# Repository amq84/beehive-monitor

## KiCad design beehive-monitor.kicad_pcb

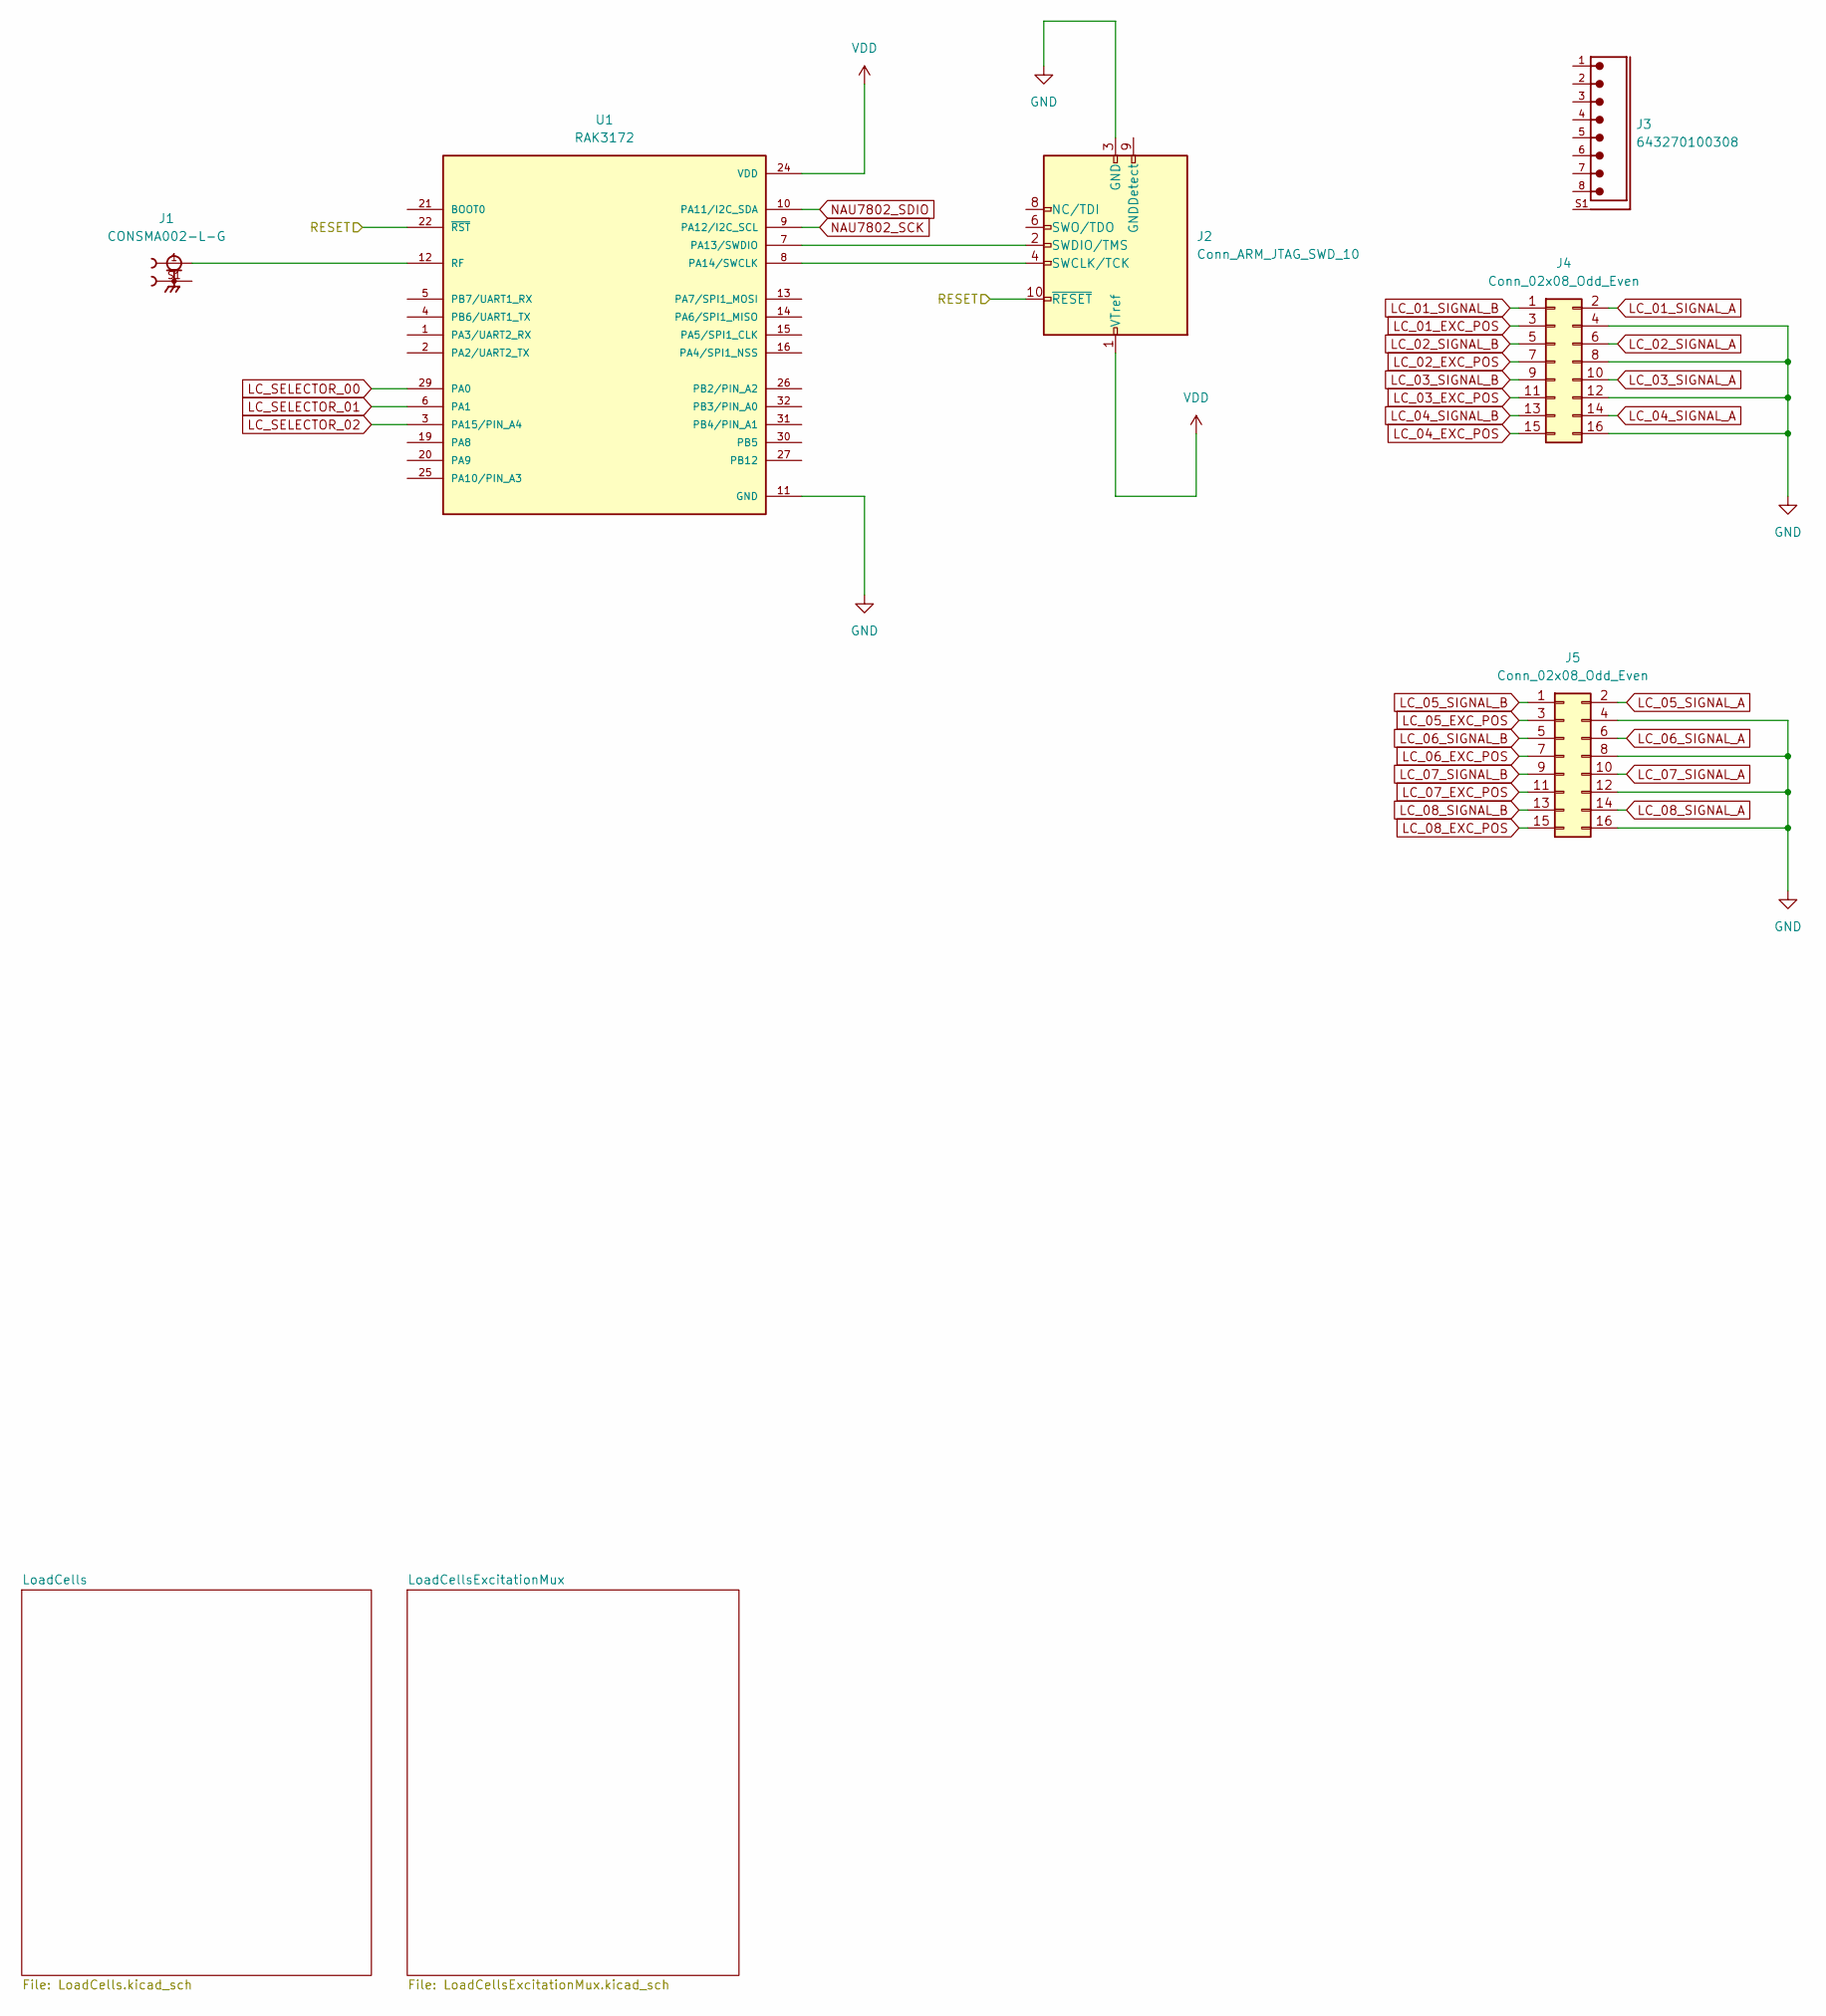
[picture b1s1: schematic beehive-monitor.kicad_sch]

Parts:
J1: CONSMA002-L-G; LINX_CONSMA002-L-G
J2: Conn_ARM_JTAG_SWD_10; PinHeader_2x05_P1.27mm_Vertical
J3: 643270100308
J4, J5: Conn_02x08_Odd_Even; PinHeader_2x08_P2.54mm_Horizontal
U1: RAK3172; XCVR_RAK3172; PARTREV 20/02/2026

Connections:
/RESET: J2.10 (~RESET), U1.22 (~RST)
GND: J2.3 (GND), J2.5 (GND), J4.4, J4.8, J4.12, J4.16, J5.4, J5.8, J5.12, J5.16, U1.11 (GND), U1.17 (GND), U1.18 (GND), U1.23 (GND), U1.28 (GND); also elsewhere on the board
LC_01_EXC_POS: J4.3; also elsewhere on the board
LC_01_SIGNAL_A: J4.2; also elsewhere on the board
LC_01_SIGNAL_B: J4.1; also elsewhere on the board
LC_02_EXC_POS: J4.7; also elsewhere on the board
LC_02_SIGNAL_A: J4.6; also elsewhere on the board
LC_02_SIGNAL_B: J4.5; also elsewhere on the board
LC_03_EXC_POS: J4.11; also elsewhere on the board
LC_03_SIGNAL_A: J4.10; also elsewhere on the board
LC_03_SIGNAL_B: J4.9; also elsewhere on the board
LC_04_EXC_POS: J4.15; also elsewhere on the board
LC_04_SIGNAL_A: J4.14; also elsewhere on the board
LC_04_SIGNAL_B: J4.13; also elsewhere on the board
LC_05_EXC_POS: J5.3; also elsewhere on the board
LC_05_SIGNAL_A: J5.2; also elsewhere on the board
LC_05_SIGNAL_B: J5.1; also elsewhere on the board
LC_06_EXC_POS: J5.7; also elsewhere on the board
LC_06_SIGNAL_A: J5.6; also elsewhere on the board
LC_06_SIGNAL_B: J5.5; also elsewhere on the board
LC_07_EXC_POS: J5.11; also elsewhere on the board
LC_07_SIGNAL_A: J5.10; also elsewhere on the board
LC_07_SIGNAL_B: J5.9; also elsewhere on the board
LC_08_EXC_POS: J5.15; also elsewhere on the board
LC_08_SIGNAL_A: J5.14; also elsewhere on the board
LC_08_SIGNAL_B: J5.13; also elsewhere on the board
LC_SELECTOR_00: U1.29 (PA0); also elsewhere on the board
LC_SELECTOR_01: U1.6 (PA1); also elsewhere on the board
LC_SELECTOR_02: U1.3 (PA15/PIN_A4); also elsewhere on the board
NAU7802_SCK: U1.9 (PA12/I2C_SCL); also elsewhere on the board
NAU7802_SDIO: U1.10 (PA11/I2C_SDA); also elsewhere on the board
unnamed: J1.S1, J1.S2, J1.S3, J1.S4
unnamed: J2.4 (SWCLK/TCK), U1.8 (PA14/SWCLK)
unnamed: J2.2 (SWDIO/TMS), U1.7 (PA13/SWDIO)
unnamed: J1.1, U1.12 (RF)
VDD: J2.1 (VTref), U1.24 (VDD); also elsewhere on the board

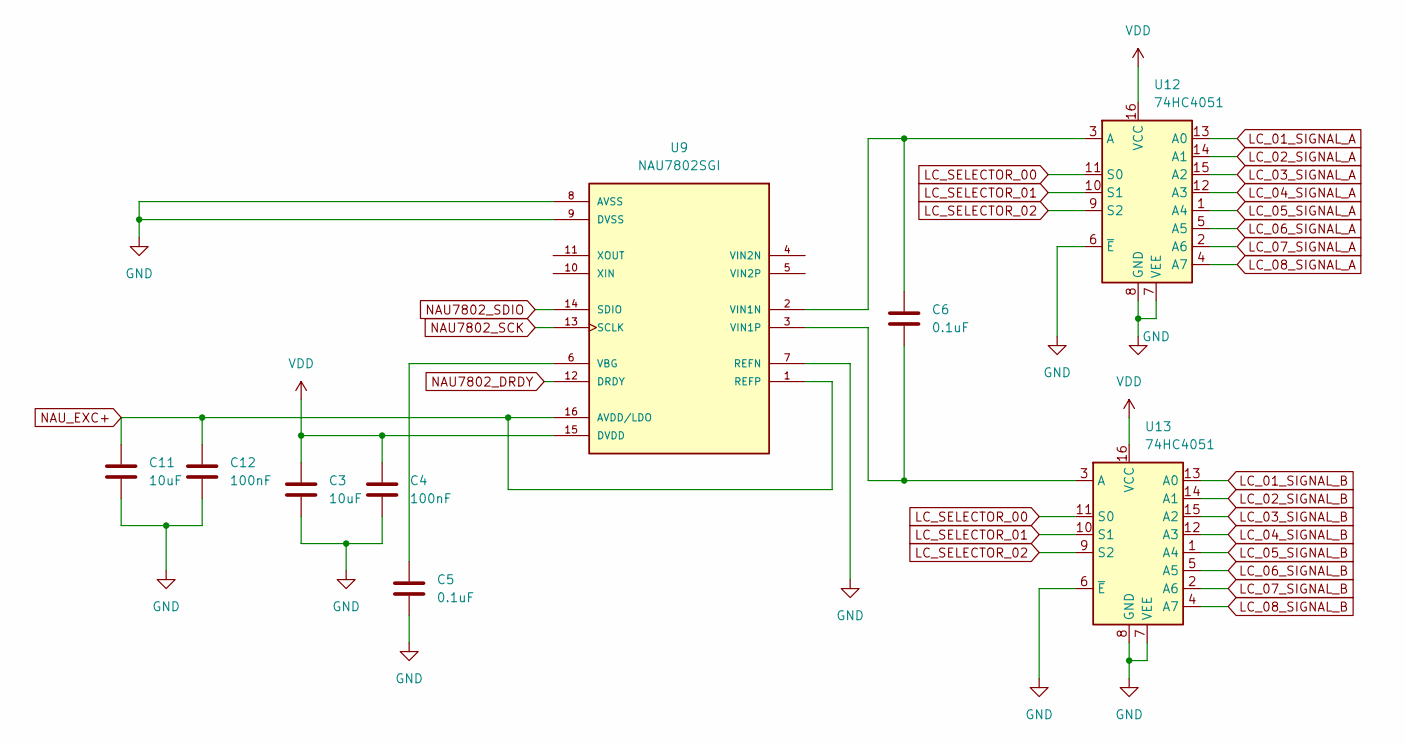
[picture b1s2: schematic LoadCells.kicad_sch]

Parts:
C3, C11: 10uF; C_0805_2012Metric
C4, C12: 100nF; C_0805_2012Metric
C5, C6: 0.1uF; C_0805_2012Metric
U9: NAU7802SGI; SOIC127P600X175-16N; PARTREV 2.6
U12, U13: 74HC4051; SO-16_3.9x9.9mm_P1.27mm

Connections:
GND: C3.2, C4.2, C5.2, C11.2, C12.2, U9.7 (REFN), U9.8 (AVSS), U9.9 (DVSS), U12.6 (~E), U12.7 (VEE), U12.8 (GND), U13.6 (~E), U13.7 (VEE), U13.8 (GND); also elsewhere on the board
LC_01_SIGNAL_A: U12.13 (A0); also elsewhere on the board
LC_01_SIGNAL_B: U13.13 (A0); also elsewhere on the board
LC_02_SIGNAL_A: U12.14 (A1); also elsewhere on the board
LC_02_SIGNAL_B: U13.14 (A1); also elsewhere on the board
LC_03_SIGNAL_A: U12.15 (A2); also elsewhere on the board
LC_03_SIGNAL_B: U13.15 (A2); also elsewhere on the board
LC_04_SIGNAL_A: U12.12 (A3); also elsewhere on the board
LC_04_SIGNAL_B: U13.12 (A3); also elsewhere on the board
LC_05_SIGNAL_A: U12.1 (A4); also elsewhere on the board
LC_05_SIGNAL_B: U13.1 (A4); also elsewhere on the board
LC_06_SIGNAL_A: U12.5 (A5); also elsewhere on the board
LC_06_SIGNAL_B: U13.5 (A5); also elsewhere on the board
LC_07_SIGNAL_A: U12.2 (A6); also elsewhere on the board
LC_07_SIGNAL_B: U13.2 (A6); also elsewhere on the board
LC_08_SIGNAL_A: U12.4 (A7); also elsewhere on the board
LC_08_SIGNAL_B: U13.4 (A7); also elsewhere on the board
LC_SELECTOR_00: U12.11 (S0), U13.11 (S0); also elsewhere on the board
LC_SELECTOR_01: U12.10 (S1), U13.10 (S1); also elsewhere on the board
LC_SELECTOR_02: U12.9 (S2), U13.9 (S2); also elsewhere on the board
NAU7802_DRDY: U9.12 (DRDY)
NAU7802_SCK: U9.13 (SCLK); also elsewhere on the board
NAU7802_SDIO: U9.14 (SDIO); also elsewhere on the board
NAU_EXC+: C11.1, C12.1, U9.1 (REFP), U9.16 (AVDD/LDO); also elsewhere on the board
unnamed: C5.1, U9.6 (VBG)
unnamed: C6.1, U9.2 (VIN1N), U12.3 (A)
unnamed: C6.2, U9.3 (VIN1P), U13.3 (A)
VDD: C3.1, C4.1, U9.15 (DVDD), U12.16 (VCC), U13.16 (VCC); also elsewhere on the board

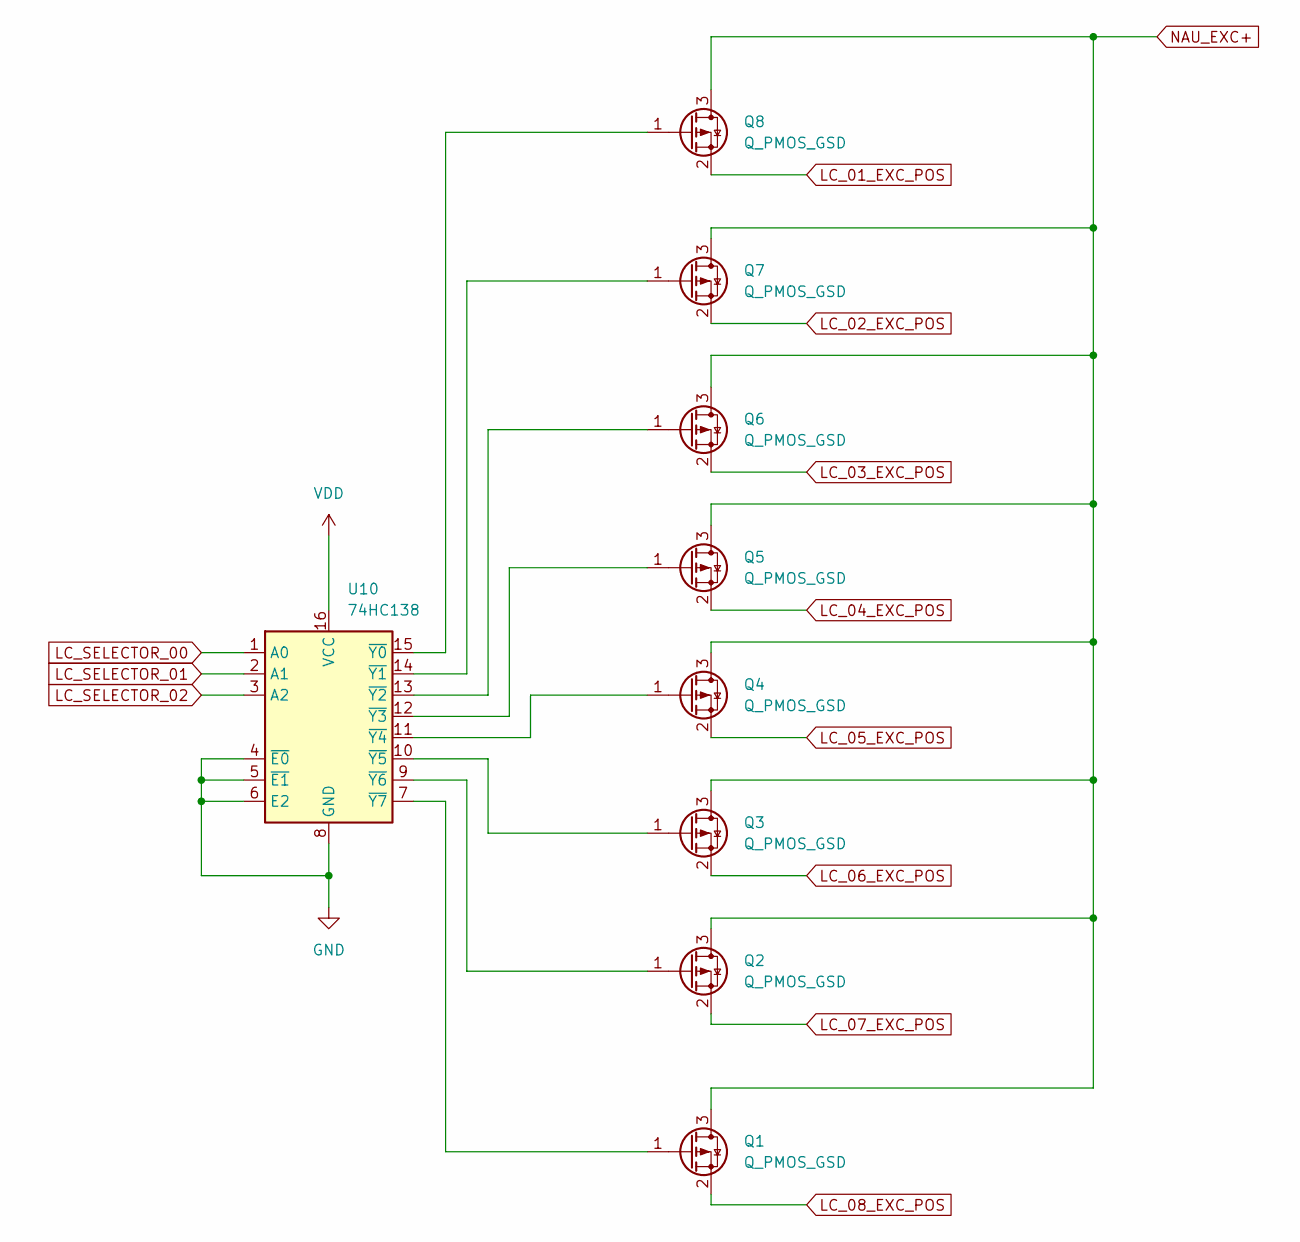
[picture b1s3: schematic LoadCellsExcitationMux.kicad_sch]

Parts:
Q1, Q2, Q3, Q4, Q5, Q6, Q7, Q8: Q_PMOS_GSD; SOT-23
U10: 74HC138; SOIC-16_3.9x9.9mm_P1.27mm

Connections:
GND: U10.4 (~E0), U10.5 (~E1), U10.6 (E2), U10.8 (GND); also elsewhere on the board
LC_01_EXC_POS: Q8.2 (S); also elsewhere on the board
LC_02_EXC_POS: Q7.2 (S); also elsewhere on the board
LC_03_EXC_POS: Q6.2 (S); also elsewhere on the board
LC_04_EXC_POS: Q5.2 (S); also elsewhere on the board
LC_05_EXC_POS: Q4.2 (S); also elsewhere on the board
LC_06_EXC_POS: Q3.2 (S); also elsewhere on the board
LC_07_EXC_POS: Q2.2 (S); also elsewhere on the board
LC_08_EXC_POS: Q1.2 (S); also elsewhere on the board
LC_SELECTOR_00: U10.1 (A0); also elsewhere on the board
LC_SELECTOR_01: U10.2 (A1); also elsewhere on the board
LC_SELECTOR_02: U10.3 (A2); also elsewhere on the board
NAU_EXC+: Q1.3 (D), Q2.3 (D), Q3.3 (D), Q4.3 (D), Q5.3 (D), Q6.3 (D), Q7.3 (D), Q8.3 (D); also elsewhere on the board
unnamed: Q1.1 (G), U10.7 (~Y7)
unnamed: Q2.1 (G), U10.9 (~Y6)
unnamed: Q3.1 (G), U10.10 (~Y5)
unnamed: Q4.1 (G), U10.11 (~Y4)
unnamed: Q5.1 (G), U10.12 (~Y3)
unnamed: Q6.1 (G), U10.13 (~Y2)
unnamed: Q7.1 (G), U10.14 (~Y1)
unnamed: Q8.1 (G), U10.15 (~Y0)
VDD: U10.16 (VCC); also elsewhere on the board

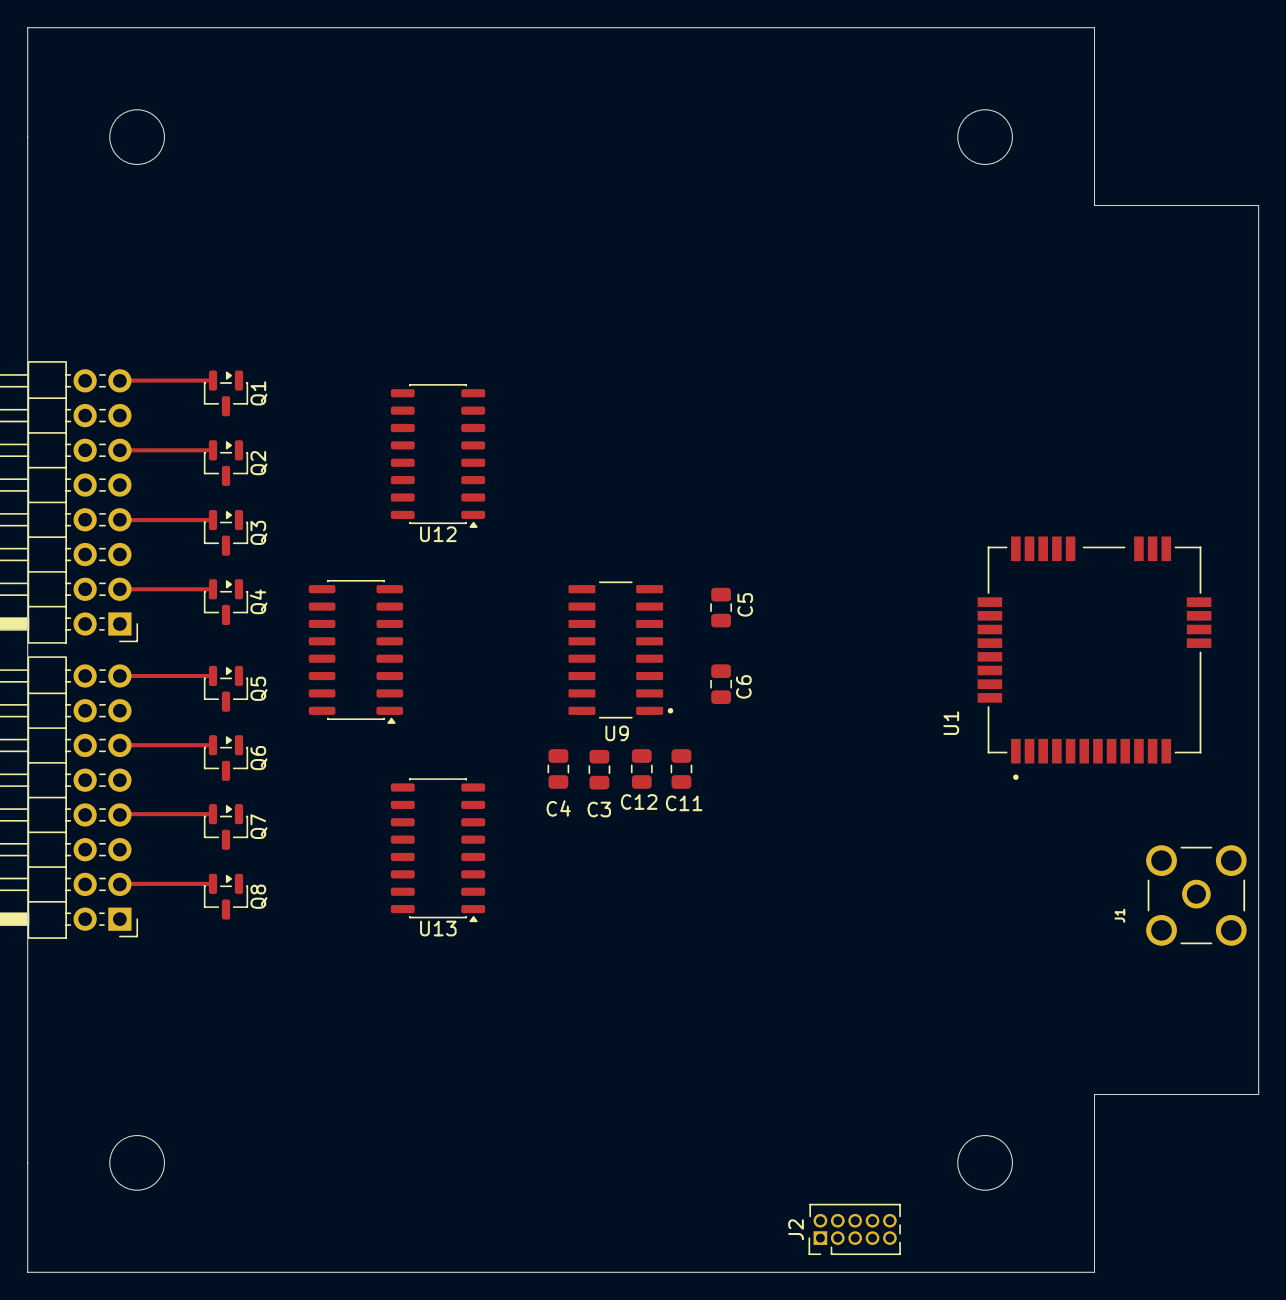
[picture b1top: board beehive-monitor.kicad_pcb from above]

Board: 4 copper layers, 90.0 x 91.0 mm, 23 parts (0 on the bottom side), 48 nets.

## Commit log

2026-05-13 First
2026-05-21 Board
